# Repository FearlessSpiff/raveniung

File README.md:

# raveniung

Keyboard designed with ergogen, heavenly inspired by the reviung34

### First time setup

* Install ergogen: `npm install -g ergogen`
* Get footprints from ceoloide: `git clone https://github.com/ceoloide/ergogen-footprints ergogen/footprints/ceoloide`
* For case build install `npm install -g @jscad/cli`

## v0.1 for Cirque Trackpad

### Build

```bash
cd ergogen
cp config-v0.1.yaml config.yaml
ergogen .
```

or for building including the left case:

```bash
ergogen . && npx @jscad/cli@1 output/cases/LeftCase.jscad -of stla
```

### Notes

* mirror right case and cirque holder!

## v0.2 for Azoteq TPS65 touchpad

### Build

```bash
cd ergogen
cp config-v0.2.yaml config.yaml
ergogen .
```

or for building including the cases:

```bash
ergogen . && npx @jscad/cli@1 output/cases/Case.jscad -of stla && npx @jscad/cli@1 output/cases/TouchpadCase.jscad -of stla
```

### TODO

## Notes

* Mount TPS65 so that FFC connector is further away from PCB connector. On left side when looking from bottom
* Use straight FFC cable (both blues on same side)
* Ply 90 degrees in the middle of the touchpad PCB
* Use FFC connector with connections on bottom (Verify before soldering!)
* For V2 use 8mm standoffs for the touchpad to make it look neater

### Laser cutting (CR-Falcon Laser 10W)

#### Flux Oak Wood 3mm

* Cut 3 times with 4mm/s 90% constant power
* Kerf: +0.1mm

#### Acryl 3mm

* Kerf Switch-Holes: -0.15mm
* Kerf Rand: +0.2mm

#### For 3d printed  case and laser cut case

* top-foam-plate: 1mm thick, cut 15mm/s 90%
* bottom-foam-plate: 3mm thick, cut 12mm/s 90% 2 passes

### Measurements

#### With PCB as top-plate and 3mm acryl top middle plate

* Standoffs must be 6mm high, 3mm diameter
* Screw from bottom M2x6mm (6.8mm total)
* Screw from top M2x4mm (4.8mm total)

#### With acryl as top-plate and 2mm? acryl top middle plate

* Standoffs must be 6mm
* Screw from bottom and bottom M2x6mm (6.8mm total)

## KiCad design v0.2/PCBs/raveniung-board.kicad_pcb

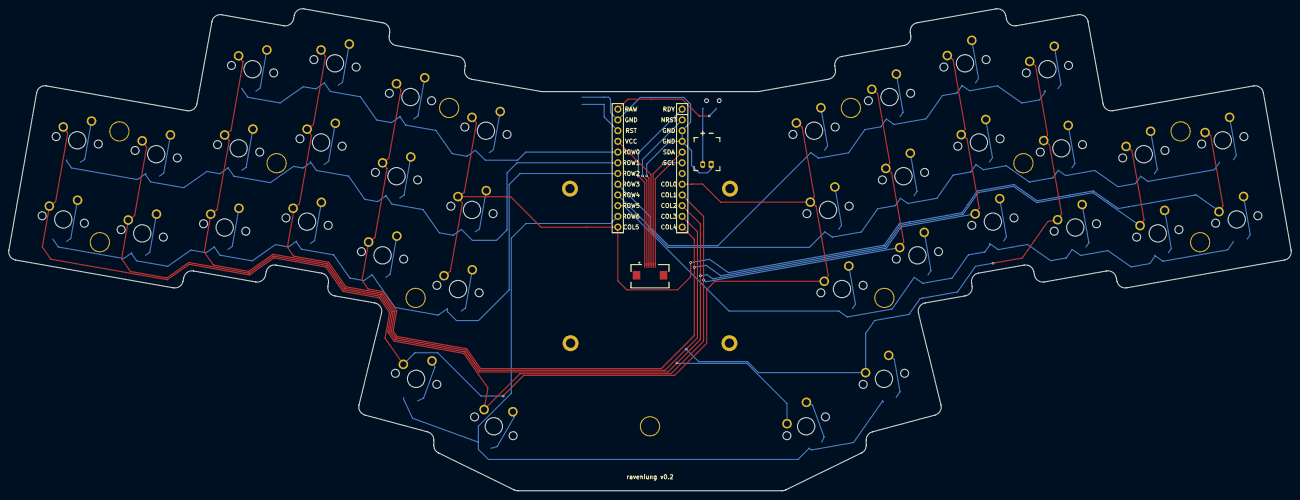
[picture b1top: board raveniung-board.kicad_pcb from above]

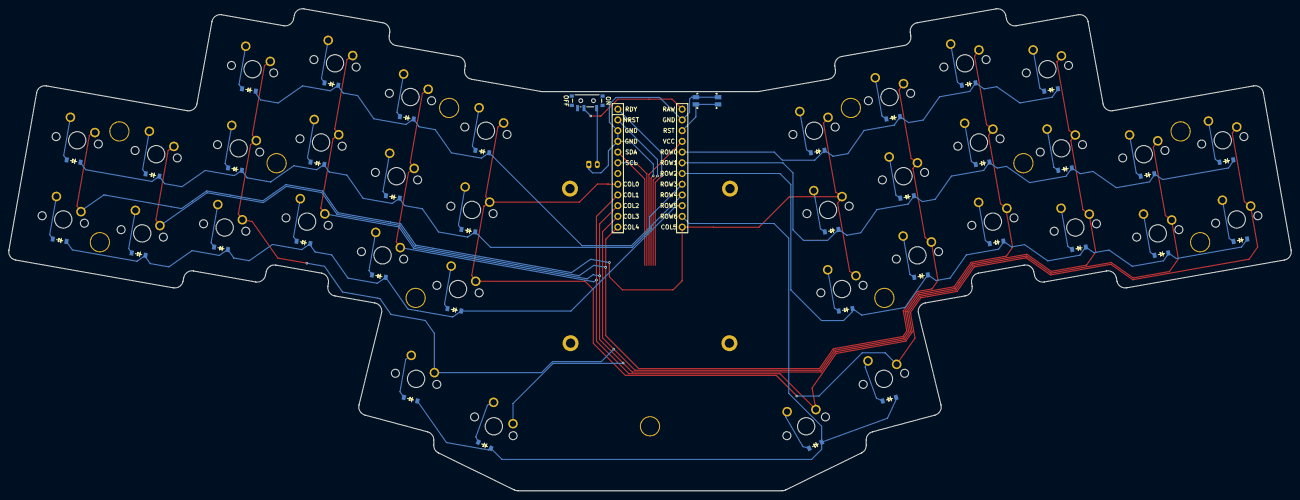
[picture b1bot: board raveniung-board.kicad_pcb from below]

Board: 2 copper layers, 304.0 x 114.2 mm, 92 parts (74 on the bottom side), 58 nets.

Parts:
D1, D2, D3, D4, D5, D6, D7, D8, D9, D10, D11, D12, D13, D14, D15, D16, D17, D18, D19, D20, D21, D22, D23, D24, D25, D26, D27, D28, D29, D30, D31, D32, D33, D34, D35, D36: diode_tht_sod123
FFC1: FPC-SMD_FPC050A004
H1, H2, H3, H4: mounting_hole_plated
JST1: battery_connector_jst_ph_2
MCU1: mcu_nice_nano
MH1, MH2, MH3, MH4, MH5, MH6, MH7, MH8, MH9, MH10, MH11: mounting_hole_npth
PWR1: power_switch_smd_side
RST1: reset_switch_smd_side
S1, S2, S3, S4, S5, S6, S7, S8, S9, S10, S11, S12, S13, S14, S15, S16, S17, S18, S19, S20, S21, S22, S23, S24, S25, S26, S27, S28, S29, S30, S31, S32, S33, S34, S35, S36: switch_mx

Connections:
BAT_P: JST1.2, PWR1.1
COL0: MCU1.8, S1.2, S2.2, S30.2, S31.2, S32.2, S34.2
COL1: MCU1.9, S3.2, S4.2, S27.2, S28.2, S29.2, S33.2
COL2: MCU1.10, S5.2, S6.2, S7.2, S24.2, S25.2, S26.2, S35.2
COL3: MCU1.11, S8.2, S9.2, S10.2, S21.2, S22.2, S23.2, S36.2
COL4: MCU1.12, S11.2, S12.2, S13.2, S19.2, S20.2
COL5: MCU1.13, S14.2, S15.2, S16.2, S17.2, S18.2
GND: FFC1.3, JST1.1, MCU1.3, MCU1.4, MCU1.23, RST1.1, RST1.3
NRST: FFC1.2, MCU1.2
RAW: MCU1.24, PWR1.2
RDY: FFC1.1, MCU1.1
ROW0: D7.1, D10.1, D13.1, D16.1, MCU1.20
ROW1: D2.1, D4.1, D6.1, D9.1, D12.1, D15.1, MCU1.19
ROW2: D1.1, D3.1, D5.1, D8.1, D11.1, D14.1, MCU1.18
ROW3: D23.1, D26.1, D29.1, D32.1, MCU1.17
ROW4: D18.1, D20.1, D22.1, D25.1, D28.1, D31.1, MCU1.16
ROW5: D17.1, D19.1, D21.1, D24.1, D27.1, D30.1, MCU1.15
ROW6: D33.1, D34.1, D35.1, D36.1, MCU1.14
RST: MCU1.22, RST1.2, RST1.4
SCL: FFC1.5, MCU1.6
SDA: FFC1.6, MCU1.5
VCC: FFC1.4, MCU1.21
index_bottom: D11.2, S11.1
index_home: D12.2, S12.1
index_top: D13.2, S13.1
inner_bottom: D14.2, S14.1
inner_home: D15.2, S15.1
inner_thumb: D33.2, S33.1
inner_top: D16.2, S16.1
middle_bottom: D8.2, S8.1
middle_home: D9.2, S9.1
middle_top: D10.2, S10.1
mirror_index_bottom: D27.2, S27.1
mirror_index_home: D28.2, S28.1
mirror_index_top: D29.2, S29.1
mirror_inner_bottom: D30.2, S30.1
mirror_inner_home: D31.2, S31.1
mirror_inner_thumb: D35.2, S35.1
mirror_inner_top: D32.2, S32.1
mirror_middle_bottom: D24.2, S24.1
mirror_middle_home: D25.2, S25.1
mirror_middle_top: D26.2, S26.1
mirror_outer_bottom: D17.2, S17.1
mirror_outer_home: D18.2, S18.1
mirror_pinky_bottom: D19.2, S19.1
mirror_pinky_home: D20.2, S20.1
mirror_reachy_thumb: D36.2, S36.1
mirror_ring_bottom: D21.2, S21.1
mirror_ring_home: D22.2, S22.1
mirror_ring_top: D23.2, S23.1
outer_bottom: D1.2, S1.1
outer_home: D2.2, S2.1
pinky_bottom: D3.2, S3.1
pinky_home: D4.2, S4.1
reachy_thumb: D34.2, S34.1
ring_bottom: D5.2, S5.1
ring_home: D6.2, S6.1
ring_top: D7.2, S7.1

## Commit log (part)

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2024-12-04 add initial ergogen definition
2024-12-04 add outlines and some things on the pcb
2024-12-04 add mac stuff to git ignore
2024-12-05 add ceoloide footprints
2024-12-05 add reviung41 style keyboard matrix and wiring
2024-12-08 add correct top plate with cherry cutouts
2024-12-11 before standoffs
2024-12-11 add standoffs, comment out unknown parts for celoide ergogen
2024-12-11 switch to 10 degree angle, more like reviung34
2024-12-11 add mounting holes and better thumb position
2024-12-12 better thumb position, fixes and simlplifications
2024-12-12 add battery, mounting holes and standoffs to pcb
2024-12-12 add top plate pcb
2024-12-12 fix cover angles
2024-12-12 add version label to pcbs
2024-12-12 change reset switch to smd one and place reset and power switch on top of pcb
2024-12-13 add bottom plate
2024-12-17 move pinky bottom mount hole a bit less to the side
2024-12-19 use ceoloide diode
2024-12-19 completely rectangular board form
2024-12-19 add bit of style to bottom part with direct line
2024-12-19 go to square outline again and move stuff for new outline
2024-12-19 move mount holes for new board shape
2024-12-19 add measuremnts of standoffs and screws to readme.md
2024-12-19 add a simpler cover plate to show off the wood top plate if wanted
2024-12-19 document laser settings for wood plate
2024-12-19 add cirque colors according to test wiring on breadboard
2024-12-19 change pcb mounting hole radius for standoff size
2024-12-20 set keycap size to mx switch width to better see what happens with the standoff holes
2024-12-30 add breadboard wire cables and mcu pins
2024-12-31 add own 0.5mm FFC connector
2024-12-31 change switch wiring direction
2024-12-31 move battery connector inside
2024-12-31 fix header of own footprint
2025-01-04 add outline for mechanical pcb preview
2025-01-04 fix top-plate mount hole radius and add top foam plate, which is the same as the top plate atm
2025-01-04 start with bottom foam plate
2025-01-05 remove pcb mechanical preview as it is easier to be done in KiCad
2025-01-05 move battery connector to other side as it's easier for routing
2025-01-05 move battery connector for easier routing
2025-01-05 finish bottom foam plate
2025-01-05 fix foam plate hole sizes
2025-01-05 fix bottom plate hole size
2025-01-07 move power switch under mcu as there is not enough place with the top plate
2025-01-07 make the mcu cover cover more
2025-01-08 move reset and power switch to bottom
2025-01-08 change cirque mapping for easier routing
2025-01-10 remove ffc connector so that it runs on ceoloide web generator
2025-01-10 add PCBs
2025-01-10 fix thumb cluster definition
2025-01-10 fix typo and bug in mirro column net for thumb cluster
2025-01-14 make ffc side pads bigger for easier manual soldering
2025-01-14 add some unwanted kicad stuff to gitignore
2025-01-16 add power and reset switch to bottom foam plate
2025-01-16 add other kicad stuff to gitignore
2025-01-16 add v0.1 outlines and stls
2025-01-16 add routed v0.1 PCBs
2025-01-17 add v0.1 gerbers
2025-01-26 fix bottom foam plate for 0.1
2025-01-29 fix cirque direction for 0.1
2025-04-10 Add a case
    This gives error as stl has problems, that can't seem to be fixed.
    Nevertheless prints fine in Bambustudio
2026-03-14 Prepare for v0.2 release
2026-03-14 Switch PCB to 6pin FFC and inver power switch behavior
2026-03-15 First try with a TPS65 case (still with another cover)
2026-03-15 Fix case gen readme
2026-03-15 Better touchpad case with correct standoffs and fixed top plate
2026-03-15 Add touchpadcase (TODO: add hole for FFC cable)
2026-03-15 Added FFC cable hole to touchpad case
2026-03-16 Move touchpad case to the top and move the FFC cutout down
2026-03-16 Improve readme
2026-03-16 Update PCB label
2026-03-16 Add touchpad overlay scad and stl
2026-03-17 Add v0.2 stuff before finishing PCB
2026-03-17 Fix top-plate label
2026-03-17 Add finished kicad pcb inclusive gerbers
2026-03-17 Add finished kicad top plate inclusive gerbers
2026-03-23 Add outline gcode for CR-Falcon
2026-03-23 Fix cut times
2026-03-24 Better parameters for cutting wood
2026-04-09 Update touchpad case for smaller 8mm standoffs
2026-04-23 Add 3mm top foam plate gcode for lasercutter
2026-06-20 Add exposed touchpad case to be able to use a stickered overlay
